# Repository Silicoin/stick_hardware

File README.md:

stick_hardware
==============

USB Miner Stick Hardware files

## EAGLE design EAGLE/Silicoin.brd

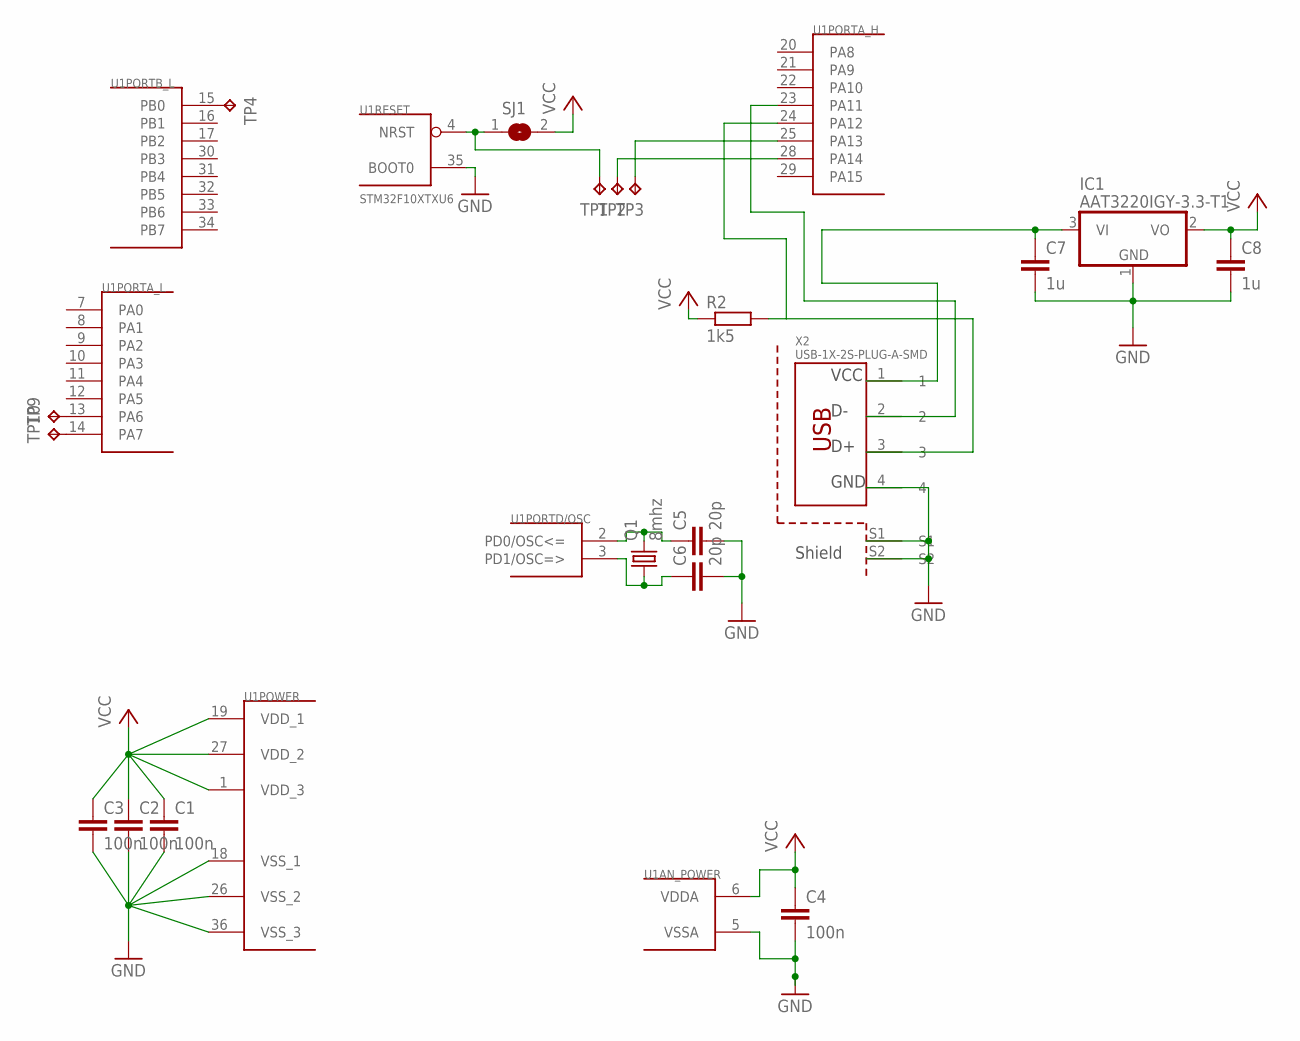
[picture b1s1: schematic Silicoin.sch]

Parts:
C1, C2, C3, C4: 100n; C0603
C5, C6: 20p; C0603
C7, C8: 1u; C0603
IC1: AAT3220IGY-3.3-T1; SOT23
Q1: 8mhz; CSM-7X-DU
R2: 1k5; R0603
SJ1: SJ
TP1, TP2, TP3, TP4, TP9, TP10: TPB2,54; B2,54
U1: STM32F10XTXU6; VFQFPN36
X2: USB-1X-2S-PLUG-A-SMD; USB-PLUG-A-SMD-2S

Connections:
GND: C1.2, C2.2, C3.2, C4.2, C5.2, C6.2, C7.2, C8.2, IC1.1 (GND), U1.5 (VSSA), U1.18 (VSS_1), U1.26 (VSS_2), U1.35 (BOOT0), U1.36 (VSS_3), X2.4, X2.S1, X2.S2
unnamed: TP4.TP, U1.15 (PB0)
unnamed: TP3.TP, U1.25 (PA13)
unnamed: SJ1.1, TP1.TP, U1.4 (NRST)
unnamed: R2.2, U1.24 (PA12), X2.3
unnamed: U1.23 (PA11), X2.2
unnamed: C5.1, Q1.2, U1.2 (PD0/OSC<=)
unnamed: C6.1, Q1.1, U1.3 (PD1/OSC=>)
unnamed: C7.1, IC1.3 (VI), X2.1
unnamed: TP2.TP, U1.28 (PA14)
unnamed: TP9.TP, U1.13 (PA6)
unnamed: TP10.TP, U1.14 (PA7)
VCC: C1.1, C2.1, C3.1, C4.1, C8.1, IC1.2 (VO), R2.1, SJ1.2, U1.1 (VDD_3), U1.6 (VDDA), U1.19 (VDD_1), U1.27 (VDD_2)

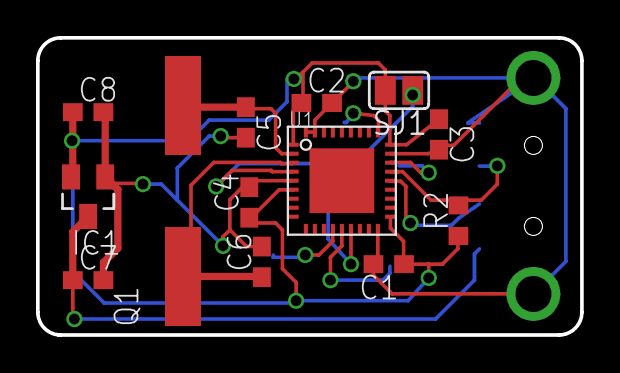
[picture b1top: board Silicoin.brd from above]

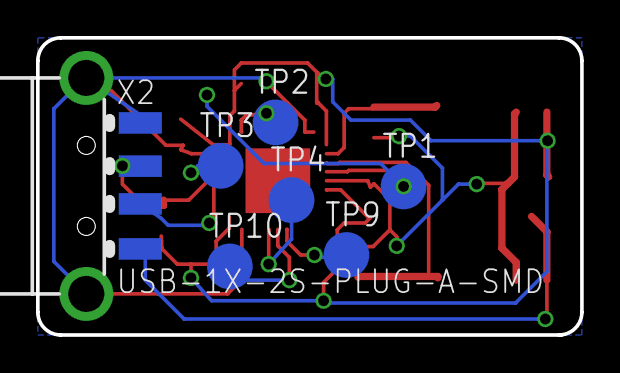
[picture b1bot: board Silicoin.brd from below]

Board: 2 copper layers, 30.2 x 16.5 mm, 20 parts (7 on the bottom side), 13 nets.

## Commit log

2014-03-23 Initial upload
